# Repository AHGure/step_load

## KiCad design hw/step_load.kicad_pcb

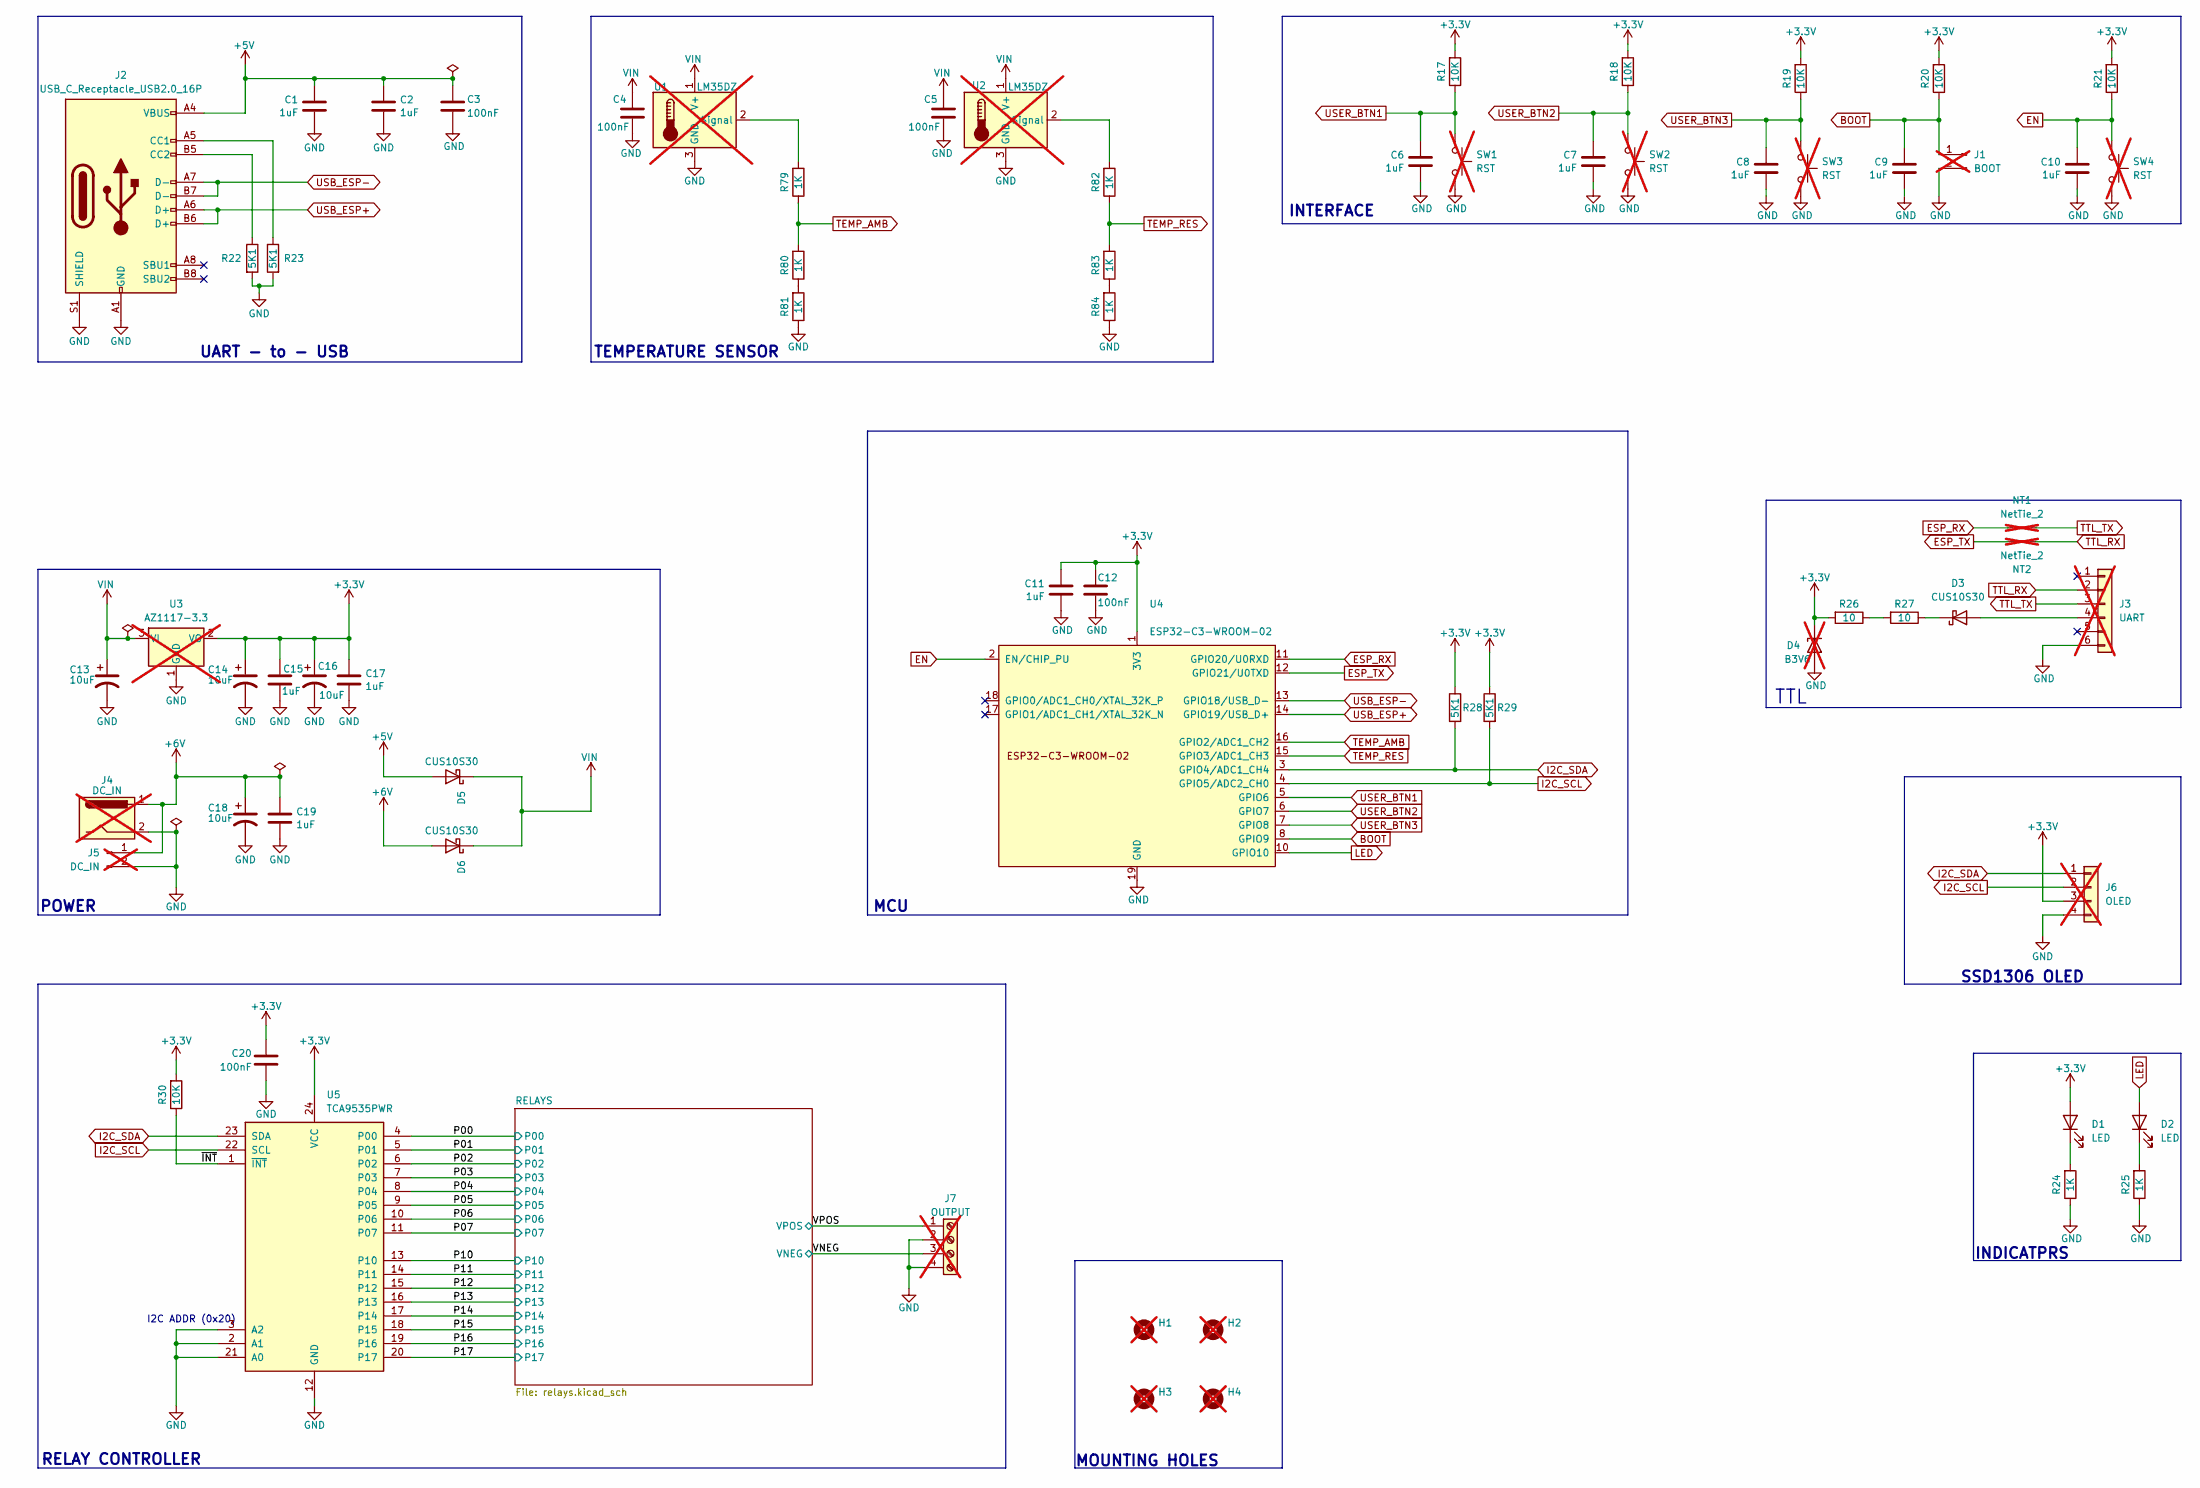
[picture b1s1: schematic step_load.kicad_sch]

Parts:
C1, C2, C6, C7, C8, C9, C10, C11, C15, C17, C19: 1uF; C_0603_1608Metric; Mfr.# CL10A105KO8NNNC; LCSC Part # C15849
C3, C4, C5, C12, C20: 100nF; C_0603_1608Metric; mfr_part CC0603KRX7R9BB104; jlc_part C14663
C13, C14, C16, C18: 10uF; CP_EIA-3216-12_Kemet-S; Mfr.# TAJA106K016RNJ; LCSC Part # C7171
D1, D2: LED; LED_0603_1608Metric; mfr_part KT-0603R; jlc_part C2286
D3: CUS10S30; D_SOD-323; Rating 30V; Mfr. Part # CUS10S30,H3F; jlc_part C146335
D4: B3V6; D_SOD-523; Mfr.# BZX585-B3V6,115; LCSC Part # C455026; not fitted
D5, D6: CUS10S30; D_SOD-323; mfr_part CUS10S30,H3F; jlc_part C146335
H1, H2, H3, H4: MountingHole; MountingHole_3.2mm_M3; not fitted
J1: BOOT; PinHeader_1x02_P2.54mm_Vertical; not fitted
J2: USB_C_Receptacle_USB2.0_16P; USB_C_Receptacle_G-Switch_GT-USB-7010ASV; mfr_part TYPE-C-31-M-12; jlc_part C165948
J3: UART; PinSocket_1x06_P2.54mm_Vertical; not fitted
J4: DC_IN; BarrelJack_Horizontal; not fitted
J5: DC_IN; PinHeader_1x02_P2.54mm_Vertical; not fitted
J6: OLED; PinSocket_1x04_P2.54mm_Vertical; not fitted
J7: OUTPUT; TerminalBlock_bornier-4_P5.08mm; LCSC Part # C557651; not fitted
NT1, NT2: NetTie_2; NetTie-2_SMD_Pad0.5mm; not fitted
R17, R18, R19, R20, R21, R30: 10K; R_0603_1608Metric; mfr_part 0603WAF1002T5E; jlc_part C25804
R22, R23, R28, R29: 5K1; R_0603_1608Metric; Mfr.# CRCW06035K10FKEA; LCSC Part # C844933
R24, R25, R79, R80, R81, R82, R83, R84: 1K; R_0603_1608Metric; mfr_part 0603WAF1001T5E; jlc_part C21190
R26, R27: 10; R_0603_1608Metric; mfr_part 0603WAF100JT5E; jlc_part C22859
SW1, SW2, SW3, SW4: RST; SW_PUSH_6mm_H5mm; Mfr. Part # B3U-1000P; not fitted
U1, U2: LM35DZ; TO-92_Inline; Mfr. Part # LM35DZ/NOPB; not fitted
U3: AZ1117-3.3; SOT-223-3_TabPin2; jlc_part C92102; not fitted
U4: ESP32-C3-WROOM-02; mfr_part ESP32-C3-WROOM-02-N4; jlc_part C2934560
U5: TCA9535PWR; TSSOP-24_4.4x7.8mm_P0.65mm; mfr_part TCA9535PWR; jlc_part C130204

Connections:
+3.3V: C11.1, C12.1, C14.1, C15.1, C16.1, C17.1, C20.1, D1.2 (A), D4.1 (K), J6.3, R17.2, R18.2, R19.2, R20.2, R21.2, R26.2, R28.1, R29.1, R30.2, U3.2 (VO), U4.1 (3V3), U5.24 (VCC); also elsewhere on the board
+5V: C1.1, C2.1, C3.1, D5.2 (A), J2.A4 (VBUS), J2.A9 (VBUS), J2.B4 (VBUS), J2.B9 (VBUS)
+6V: C18.1, C19.1, D6.2 (A), J4.1, J5.1
/P00: U5.4 (P00); also elsewhere on the board
/P01: U5.5 (P01); also elsewhere on the board
/P02: U5.6 (P02); also elsewhere on the board
/P03: U5.7 (P03); also elsewhere on the board
/P04: U5.8 (P04); also elsewhere on the board
/P05: U5.9 (P05); also elsewhere on the board
/P06: U5.10 (P06); also elsewhere on the board
/P07: U5.11 (P07); also elsewhere on the board
/P10: U5.13 (P10); also elsewhere on the board
/P11: U5.14 (P11); also elsewhere on the board
/P12: U5.15 (P12); also elsewhere on the board
/P13: U5.16 (P13); also elsewhere on the board
/P14: U5.17 (P14); also elsewhere on the board
/P15: U5.18 (P15); also elsewhere on the board
/P16: U5.19 (P16); also elsewhere on the board
/P17: U5.20 (P17); also elsewhere on the board
/VNEG: J7.3; also elsewhere on the board
/VPOS: J7.1; also elsewhere on the board
/~INT: R30.1, U5.1 (~INT)
BOOT: C9.1, J1.1, R20.1, U4.8 (GPIO9)
EN: C10.1, R21.1, SW4.1, U4.2 (EN/CHIP_PU)
ESP_RX: NT1.1, U4.11 (GPIO20/U0RXD)
ESP_TX: NT2.1, U4.12 (GPIO21/U0TXD)
GND: C1.2, C2.2, C3.2, C4.2, C5.2, C6.2, C7.2, C8.2, C9.2, C10.2, C11.2, C12.2, C13.2, C14.2, C15.2, C16.2, C17.2, C18.2, C19.2, C20.2, D4.2 (A), J1.2, J2.A1 (GND), J2.A12 (GND), J2.B1 (GND), J2.B12 (GND), J2.S1 (SHIELD), J3.6, J4.2, J5.2, J6.4, J7.2, J7.4, R22.2, R23.2, R24.1, R25.1, R81.1, R84.1, SW1.2, SW2.2, SW3.2, SW4.2, U1.3 (GND), U2.3 (GND), U3.1 (GND), U4.9 (GND), U4.19 (GND), U5.2 (A1), U5.3 (A2), U5.12 (GND), U5.21 (A0); also elsewhere on the board
I2C_SCL: J6.2, R29.2, U4.4 (GPIO5/ADC2_CH0), U5.22 (SCL)
I2C_SDA: J6.1, R28.2, U4.3 (GPIO4/ADC1_CH4), U5.23 (SDA)
LED: D2.2 (A), U4.10 (GPIO10)
unnamed: D1.1 (K), R24.2
unnamed: D2.1 (K), R25.2
unnamed: D3.2 (A), J3.4
unnamed: D3.1 (K), R27.1
unnamed: J2.A5 (CC1), R23.1
unnamed: J2.B5 (CC2), R22.1
unnamed: R26.1, R27.2
unnamed: R80.1, R81.2
unnamed: R83.1, R84.2
unnamed: R79.2, U1.2 (Signal)
unnamed: R82.2, U2.2 (Signal)
TEMP_AMB: R79.1, R80.2, U4.16 (GPIO2/ADC1_CH2)
TEMP_RES: R82.1, R83.2, U4.15 (GPIO3/ADC1_CH3)
TTL_RX: J3.2, NT2.2
TTL_TX: J3.3, NT1.2
USB_ESP+: J2.A6 (D+), J2.B6 (D+), U4.14 (GPIO19/USB_D+)
USB_ESP-: J2.A7 (D-), J2.B7 (D-), U4.13 (GPIO18/USB_D-)
USER_BTN1: C6.1, R17.1, SW1.1, U4.5 (GPIO6)
USER_BTN2: C7.1, R18.1, SW2.1, U4.6 (GPIO7)
USER_BTN3: C8.1, R19.1, SW3.1, U4.7 (GPIO8)
VIN: C4.1, C5.1, C13.1, D5.1 (K), D6.1 (K), U1.1 (V+), U2.1 (V+), U3.3 (VI)

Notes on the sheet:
UART - to - USB
RELAY CONTROLLER
MCU
TTL
INTERFACE
SSD1306 OLED
INDICATPRS
MOUNTING HOLES
TEMPERATURE SENSOR
POWER
I2C ADDR (0x20)

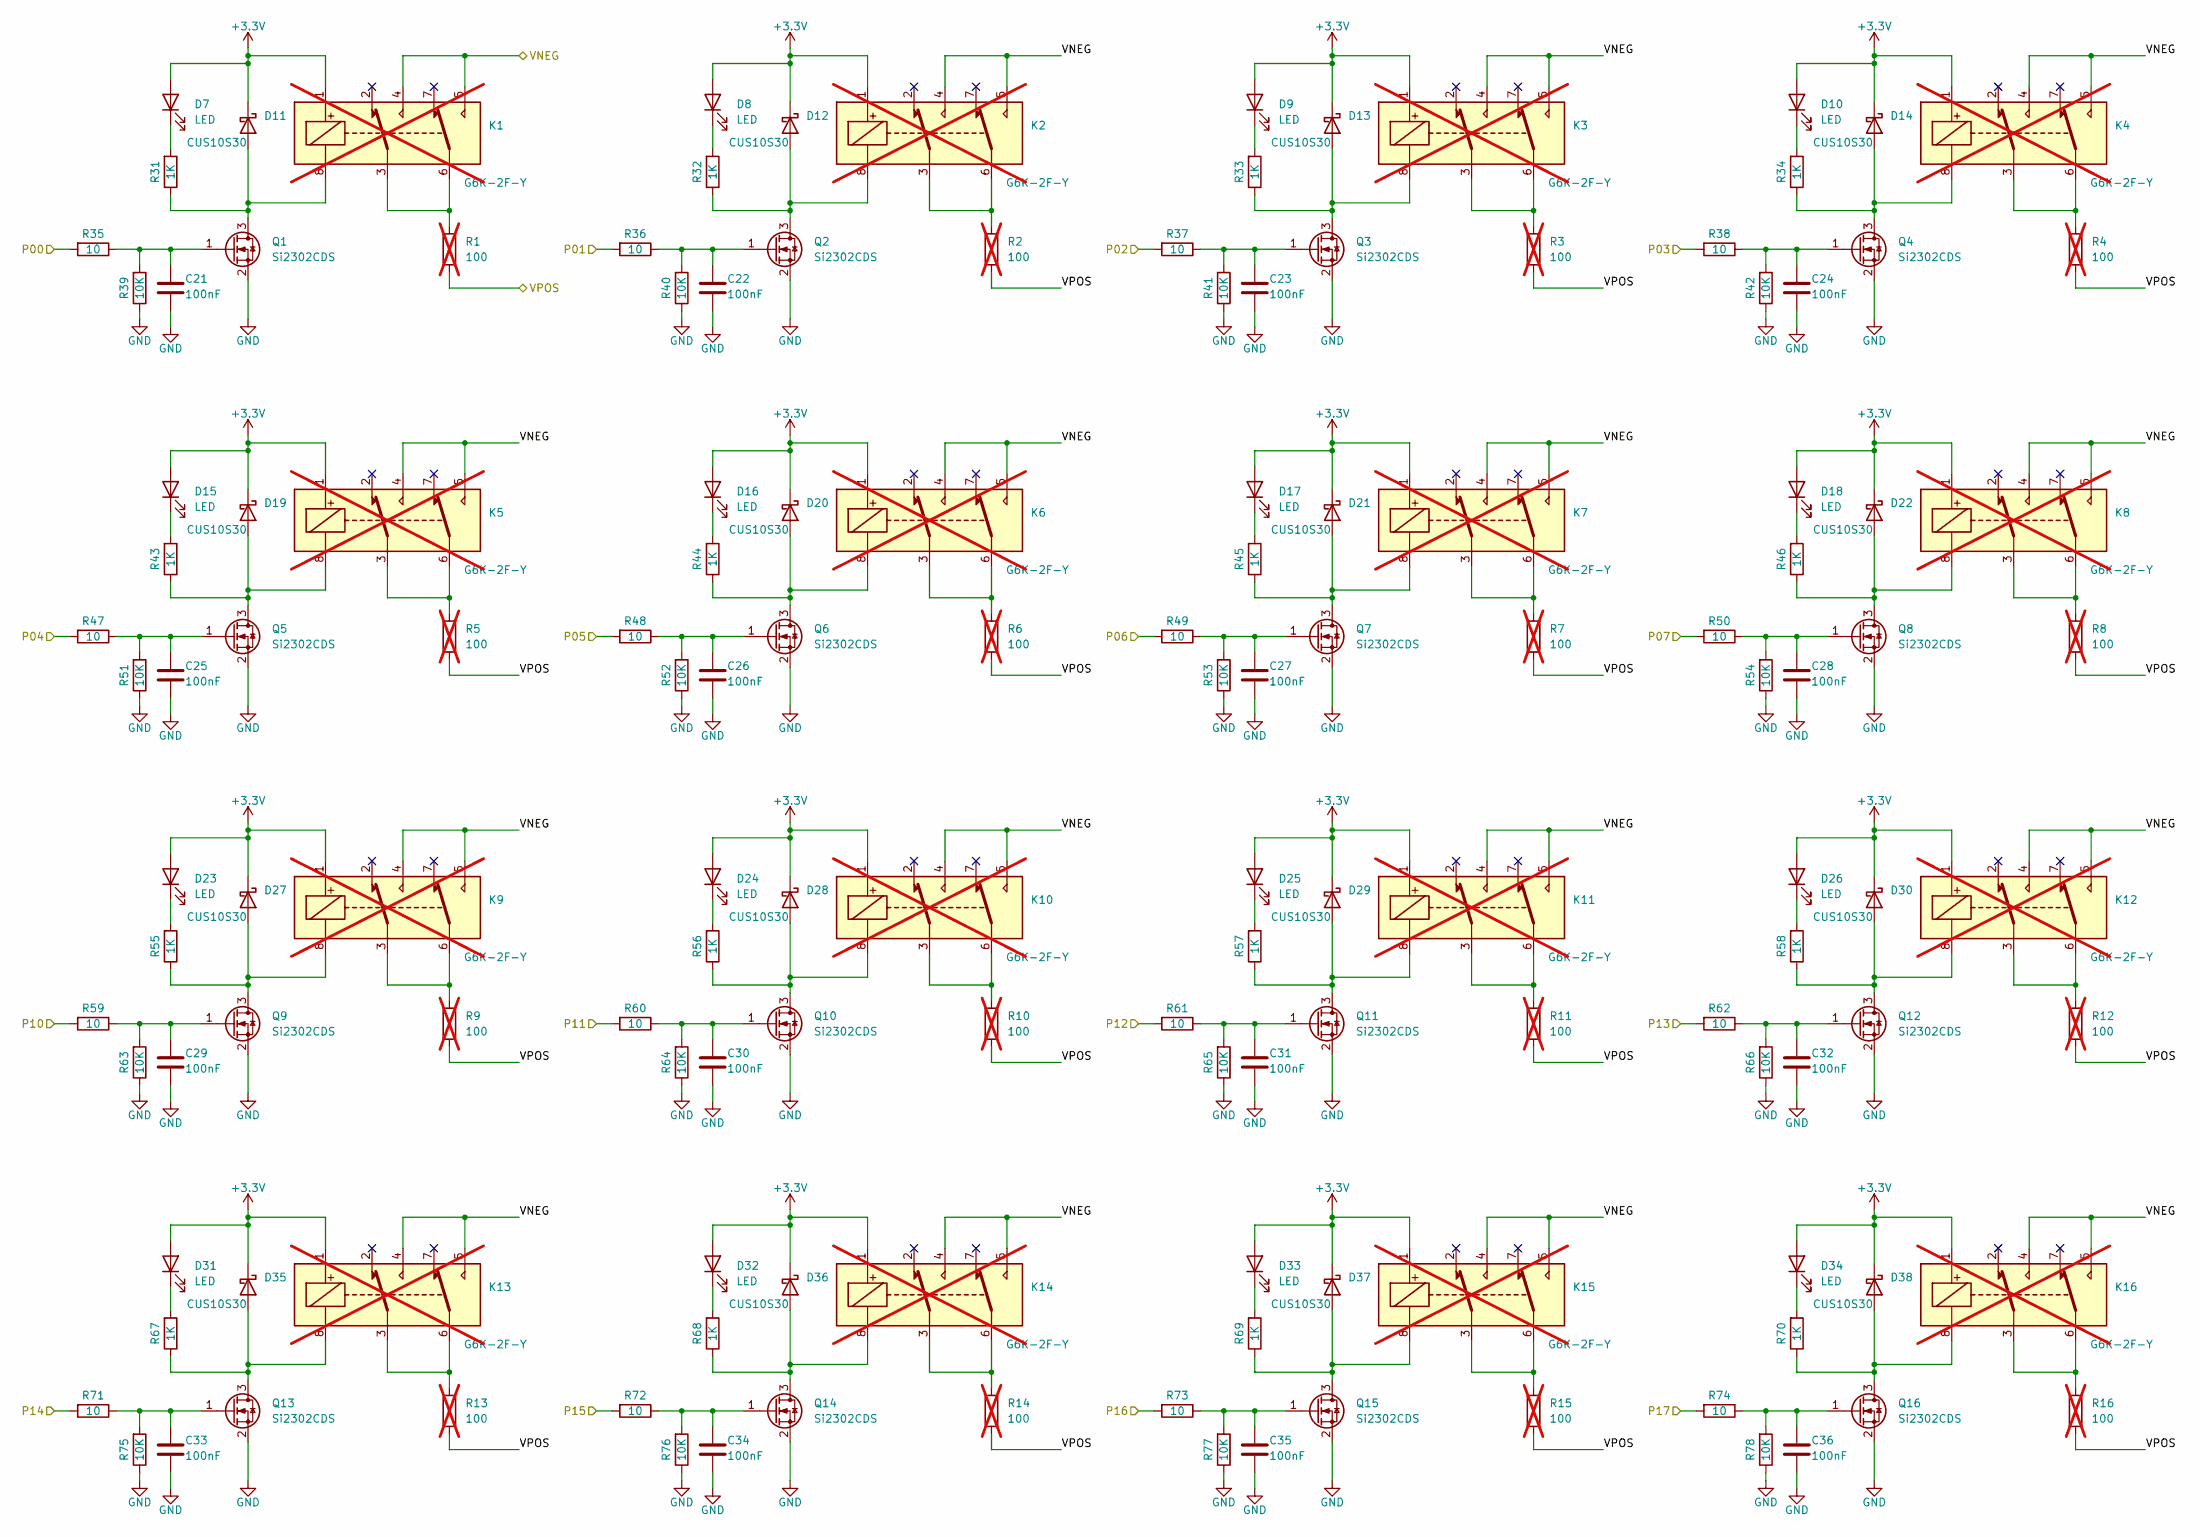
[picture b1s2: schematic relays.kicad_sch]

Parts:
C21, C22, C23, C24, C25, C26, C27, C28, C29, C30, C31, C32, C33, C34, C35, C36: 100nF; C_0603_1608Metric; mfr_part CC0603KRX7R9BB104; jlc_part C14663
D7, D8, D9, D10, D15, D16, D17, D18, D23, D24, D25, D26, D31, D32, D33, D34: LED; LED_0603_1608Metric; mfr_part KT-0603R; jlc_part C2286
D11, D12, D13, D14, D19, D20, D21, D22, D27, D28, D29, D30, D35, D36, D37, D38: CUS10S30; D_SOD-323; mfr_part CUS10S30,H3F; jlc_part C146335
K1, K2, K3, K4, K5, K6, K7, K8, K9, K10, K11, K12, K13, K14, K15, K16: G6K-2F-Y; Relay_DPDT_Omron_G6K-2F-Y; mfr_part G6K-2F-Y-TR DC3; jlc_part C2153097; not fitted
Q1, Q2, Q3, Q4, Q5, Q6, Q7, Q8, Q9, Q10, Q11, Q12, Q13, Q14, Q15, Q16: Si2302CDS; SOT-23; mfr_part Si2302CDS-T1-E3-HXY; jlc_part C22367239
R1, R2, R3, R4, R5, R6, R7, R8, R9, R10, R11, R12, R13, R14, R15, R16: 100; R_Axial_DIN0617_L17.0mm_D6.0mm_P20.32mm_Horizontal; mfr_part AC04000001000JAC00; jlc_part C1365231; not fitted
R31, R32, R33, R34, R43, R44, R45, R46, R55, R56, R57, R58, R67, R68, R69, R70: 1K; R_0603_1608Metric; mfr_part 0603WAF1001T5E; jlc_part C21190
R35, R36, R37, R38, R47, R48, R49, R50, R59, R60, R61, R62, R71, R72, R73, R74: 10; R_0603_1608Metric; mfr_part 0603WAF100JT5E; jlc_part C22859
R39, R40, R41, R42, R51, R52, R53, R54, R63, R64, R65, R66, R75, R76, R77, R78: 10K; R_0603_1608Metric; mfr_part 0603WAF1002T5E; jlc_part C25804

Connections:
+3.3V: D7.2 (A), D8.2 (A), D9.2 (A), D10.2 (A), D11.1 (K), D12.1 (K), D13.1 (K), D14.1 (K), D15.2 (A), D16.2 (A), D17.2 (A), D18.2 (A), D19.1 (K), D20.1 (K), D21.1 (K), D22.1 (K), D23.2 (A), D24.2 (A), D25.2 (A), D26.2 (A), D27.1 (K), D28.1 (K), D29.1 (K), D30.1 (K), D31.2 (A), D32.2 (A), D33.2 (A), D34.2 (A), D35.1 (K), D36.1 (K), D37.1 (K), D38.1 (K), K1.1, K2.1, K3.1, K4.1, K5.1, K6.1, K7.1, K8.1, K9.1, K10.1, K11.1, K12.1, K13.1, K14.1, K15.1, K16.1; also elsewhere on the board
/P00: R35.2; also elsewhere on the board
/P01: R36.2; also elsewhere on the board
/P02: R37.2; also elsewhere on the board
/P03: R38.2; also elsewhere on the board
/P04: R47.2; also elsewhere on the board
/P05: R48.2; also elsewhere on the board
/P06: R49.2; also elsewhere on the board
/P07: R50.2; also elsewhere on the board
/P10: R59.2; also elsewhere on the board
/P11: R60.2; also elsewhere on the board
/P12: R61.2; also elsewhere on the board
/P13: R62.2; also elsewhere on the board
/P14: R71.2; also elsewhere on the board
/P15: R72.2; also elsewhere on the board
/P16: R73.2; also elsewhere on the board
/P17: R74.2; also elsewhere on the board
/VNEG: K1.4, K1.5, K2.4, K2.5, K3.4, K3.5, K4.4, K4.5, K5.4, K5.5, K6.4, K6.5, K7.4, K7.5, K8.4, K8.5, K9.4, K9.5, K10.4, K10.5, K11.4, K11.5, K12.4, K12.5, K13.4, K13.5, K14.4, K14.5, K15.4, K15.5, K16.4, K16.5; also elsewhere on the board
/VPOS: R1.2, R2.2, R3.2, R4.2, R5.2, R6.2, R7.2, R8.2, R9.2, R10.2, R11.2, R12.2, R13.2, R14.2, R15.2, R16.2; also elsewhere on the board
GND: C21.2, C22.2, C23.2, C24.2, C25.2, C26.2, C27.2, C28.2, C29.2, C30.2, C31.2, C32.2, C33.2, C34.2, C35.2, C36.2, Q1.2 (S), Q2.2 (S), Q3.2 (S), Q4.2 (S), Q5.2 (S), Q6.2 (S), Q7.2 (S), Q8.2 (S), Q9.2 (S), Q10.2 (S), Q11.2 (S), Q12.2 (S), Q13.2 (S), Q14.2 (S), Q15.2 (S), Q16.2 (S), R39.1, R40.1, R41.1, R42.1, R51.1, R52.1, R53.1, R54.1, R63.1, R64.1, R65.1, R66.1, R75.1, R76.1, R77.1, R78.1; also elsewhere on the board
unnamed: D7.1 (K), R31.2
unnamed: D8.1 (K), R32.2
unnamed: D9.1 (K), R33.2
unnamed: D10.1 (K), R34.2
unnamed: D11.2 (A), K1.8, Q1.3 (D), R31.1
unnamed: D12.2 (A), K2.8, Q2.3 (D), R32.1
unnamed: D13.2 (A), K3.8, Q3.3 (D), R33.1
unnamed: D14.2 (A), K4.8, Q4.3 (D), R34.1
unnamed: D15.1 (K), R43.2
unnamed: D16.1 (K), R44.2
unnamed: D17.1 (K), R45.2
unnamed: D18.1 (K), R46.2
unnamed: D19.2 (A), K5.8, Q5.3 (D), R43.1
unnamed: D20.2 (A), K6.8, Q6.3 (D), R44.1
unnamed: D21.2 (A), K7.8, Q7.3 (D), R45.1
unnamed: D22.2 (A), K8.8, Q8.3 (D), R46.1
unnamed: D23.1 (K), R55.2
unnamed: D24.1 (K), R56.2
unnamed: D25.1 (K), R57.2
unnamed: D26.1 (K), R58.2
unnamed: D27.2 (A), K9.8, Q9.3 (D), R55.1
unnamed: D28.2 (A), K10.8, Q10.3 (D), R56.1
unnamed: D29.2 (A), K11.8, Q11.3 (D), R57.1
unnamed: D30.2 (A), K12.8, Q12.3 (D), R58.1
unnamed: D31.1 (K), R67.2
unnamed: D32.1 (K), R68.2
unnamed: D33.1 (K), R69.2
unnamed: D34.1 (K), R70.2
unnamed: D35.2 (A), K13.8, Q13.3 (D), R67.1
unnamed: D36.2 (A), K14.8, Q14.3 (D), R68.1
unnamed: D37.2 (A), K15.8, Q15.3 (D), R69.1
unnamed: D38.2 (A), K16.8, Q16.3 (D), R70.1
unnamed: K1.3, K1.6, R1.1
unnamed: K2.3, K2.6, R2.1
unnamed: K3.3, K3.6, R3.1
unnamed: K4.3, K4.6, R4.1
unnamed: K5.3, K5.6, R5.1
unnamed: K6.3, K6.6, R6.1
unnamed: K7.3, K7.6, R7.1
unnamed: K8.3, K8.6, R8.1
unnamed: K9.3, K9.6, R9.1
unnamed: K10.3, K10.6, R10.1
unnamed: K11.3, K11.6, R11.1
unnamed: K12.3, K12.6, R12.1
unnamed: K13.3, K13.6, R13.1
unnamed: K14.3, K14.6, R14.1
unnamed: K15.3, K15.6, R15.1
unnamed: K16.3, K16.6, R16.1
unnamed: C21.1, Q1.1 (G), R35.1, R39.2
unnamed: C22.1, Q2.1 (G), R36.1, R40.2
unnamed: C23.1, Q3.1 (G), R37.1, R41.2
unnamed: C24.1, Q4.1 (G), R38.1, R42.2
unnamed: C25.1, Q5.1 (G), R47.1, R51.2
unnamed: C26.1, Q6.1 (G), R48.1, R52.2
unnamed: C27.1, Q7.1 (G), R49.1, R53.2
unnamed: C28.1, Q8.1 (G), R50.1, R54.2
unnamed: C29.1, Q9.1 (G), R59.1, R63.2
unnamed: C30.1, Q10.1 (G), R60.1, R64.2
unnamed: C31.1, Q11.1 (G), R61.1, R65.2
unnamed: C32.1, Q12.1 (G), R62.1, R66.2
unnamed: C33.1, Q13.1 (G), R71.1, R75.2
unnamed: C34.1, Q14.1 (G), R72.1, R76.2
unnamed: C35.1, Q15.1 (G), R73.1, R77.2
unnamed: C36.1, Q16.1 (G), R74.1, R78.2

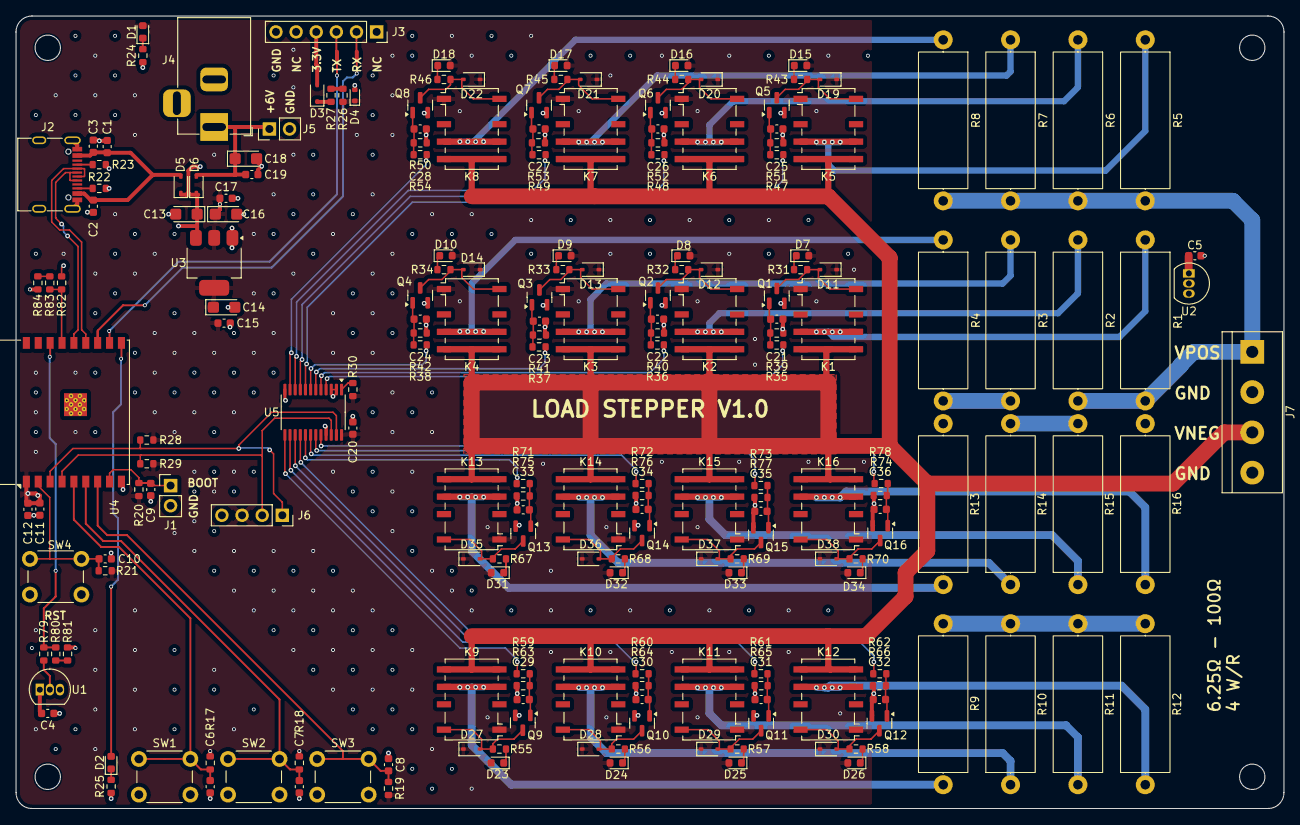
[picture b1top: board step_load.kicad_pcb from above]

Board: 4 copper layers, 160.0 x 100.0 mm, 212 parts (0 on the bottom side), 115 nets.

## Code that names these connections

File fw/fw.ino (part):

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#define LED_PIN             10
#define I2C_IOEXP_ADDRESS   0x20
#define I2C_OLED_ADDRESS    0x3C
#define I2C_SDA_PIN         4
#define I2C_SCL_PIN         5

#define SCREEN_WIDTH        128
#define SCREEN_HEIGHT       64
#define OLED_RESET          -1

/*BUTTONS*/
#define USER_BTN1_PIN   6
#define USER_BTN2_PIN   7
#define USER_BTN3_PIN   8

#define TEMP_AMB_PIN    2
#define TEMP_RES_PIN    3

#define DEBOUNCE_MS     200

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  noInterrupts();  // Disable interrupts during processing
  uint64_t currentTime = millis();

  if ( digitalRead(USER_BTN1_PIN) == LOW ) {
      if (currentTime - lastBtn1Interrupt > DEBOUNCE_MS) {
        btn1Pressed = 1;
        lastBtn1Interrupt = currentTime;
      }
  } else if ( digitalRead(USER_BTN2_PIN) == LOW ) {
      if (currentTime - lastBtn2Interrupt > DEBOUNCE_MS) {
        btn2Pressed = 1;
        lastBtn2Interrupt = currentTime;
      }
  } else if ( digitalRead(USER_BTN3_PIN) == LOW ) {
      if (currentTime - lastBtn3Interrupt > DEBOUNCE_MS) {
        btn3Pressed = 1;
        lastBtn3Interrupt = currentTime;
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    delay(100);
    Serial.println("Starting setup...");
    // Configure button pins with internal pull-up resistors
    pinMode(USER_BTN1_PIN, INPUT);
    pinMode(USER_BTN2_PIN, INPUT);
    pinMode(USER_BTN3_PIN, INPUT);
    pinMode(TEMP_AMB_PIN, INPUT);
    pinMode(TEMP_RES_PIN, INPUT);
    Wire.begin(I2C_SDA_PIN, I2C_SCL_PIN);
    TCA.begin();
    if ( !display.begin(SSD1306_SWITCHCAPVCC, I2C_OLED_ADDRESS) ) {
      Serial.println(F("SSD1306 connection failed!"));
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    // Display initial state (all relays off)
    setResistorAndDelay(selectedResistor);

    attachInterrupt(digitalPinToInterrupt(USER_BTN1_PIN),
                    handleBtnPress, FALLING);
    attachInterrupt(digitalPinToInterrupt(USER_BTN2_PIN),
                    handleBtnPress, FALLING);
    attachInterrupt(digitalPinToInterrupt(USER_BTN3_PIN),
                    handleBtnPress, FALLING);
}

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
void getTempAndDisplay() {
    // Read LM35DZ sensor value
    int tempResistor = analogRead(TEMP_RES_PIN);
    int tempAmbient = analogRead(TEMP_AMB_PIN);
    float temperatureC = (tempResistor * 3.3 * 100.0) / 4096.0;
    float temperatureAmbC = (tempAmbient * 3.3 * 100.0) / 4096.0;
    char temperatureCStr[6];
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
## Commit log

2025-10-26 pcb update
2025-10-28 sch & pcb update
2025-11-05 pcb completed
2025-11-18 minor update
2025-11-18 Swapt USB+ (A6 & B6) and USB- (A7 & B7) connection, fix the Device Unknown issue
2025-11-18 fw initial commit
2025-11-19 fw update
2025-11-19 relay run through
2025-11-20 ioexpander glitch fixed
2025-11-20 ci issue fixed
2025-11-23 sch update
2026-02-15 fw minor update

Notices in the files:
fw/fw.ino:
Copyright 2025 AHGure
